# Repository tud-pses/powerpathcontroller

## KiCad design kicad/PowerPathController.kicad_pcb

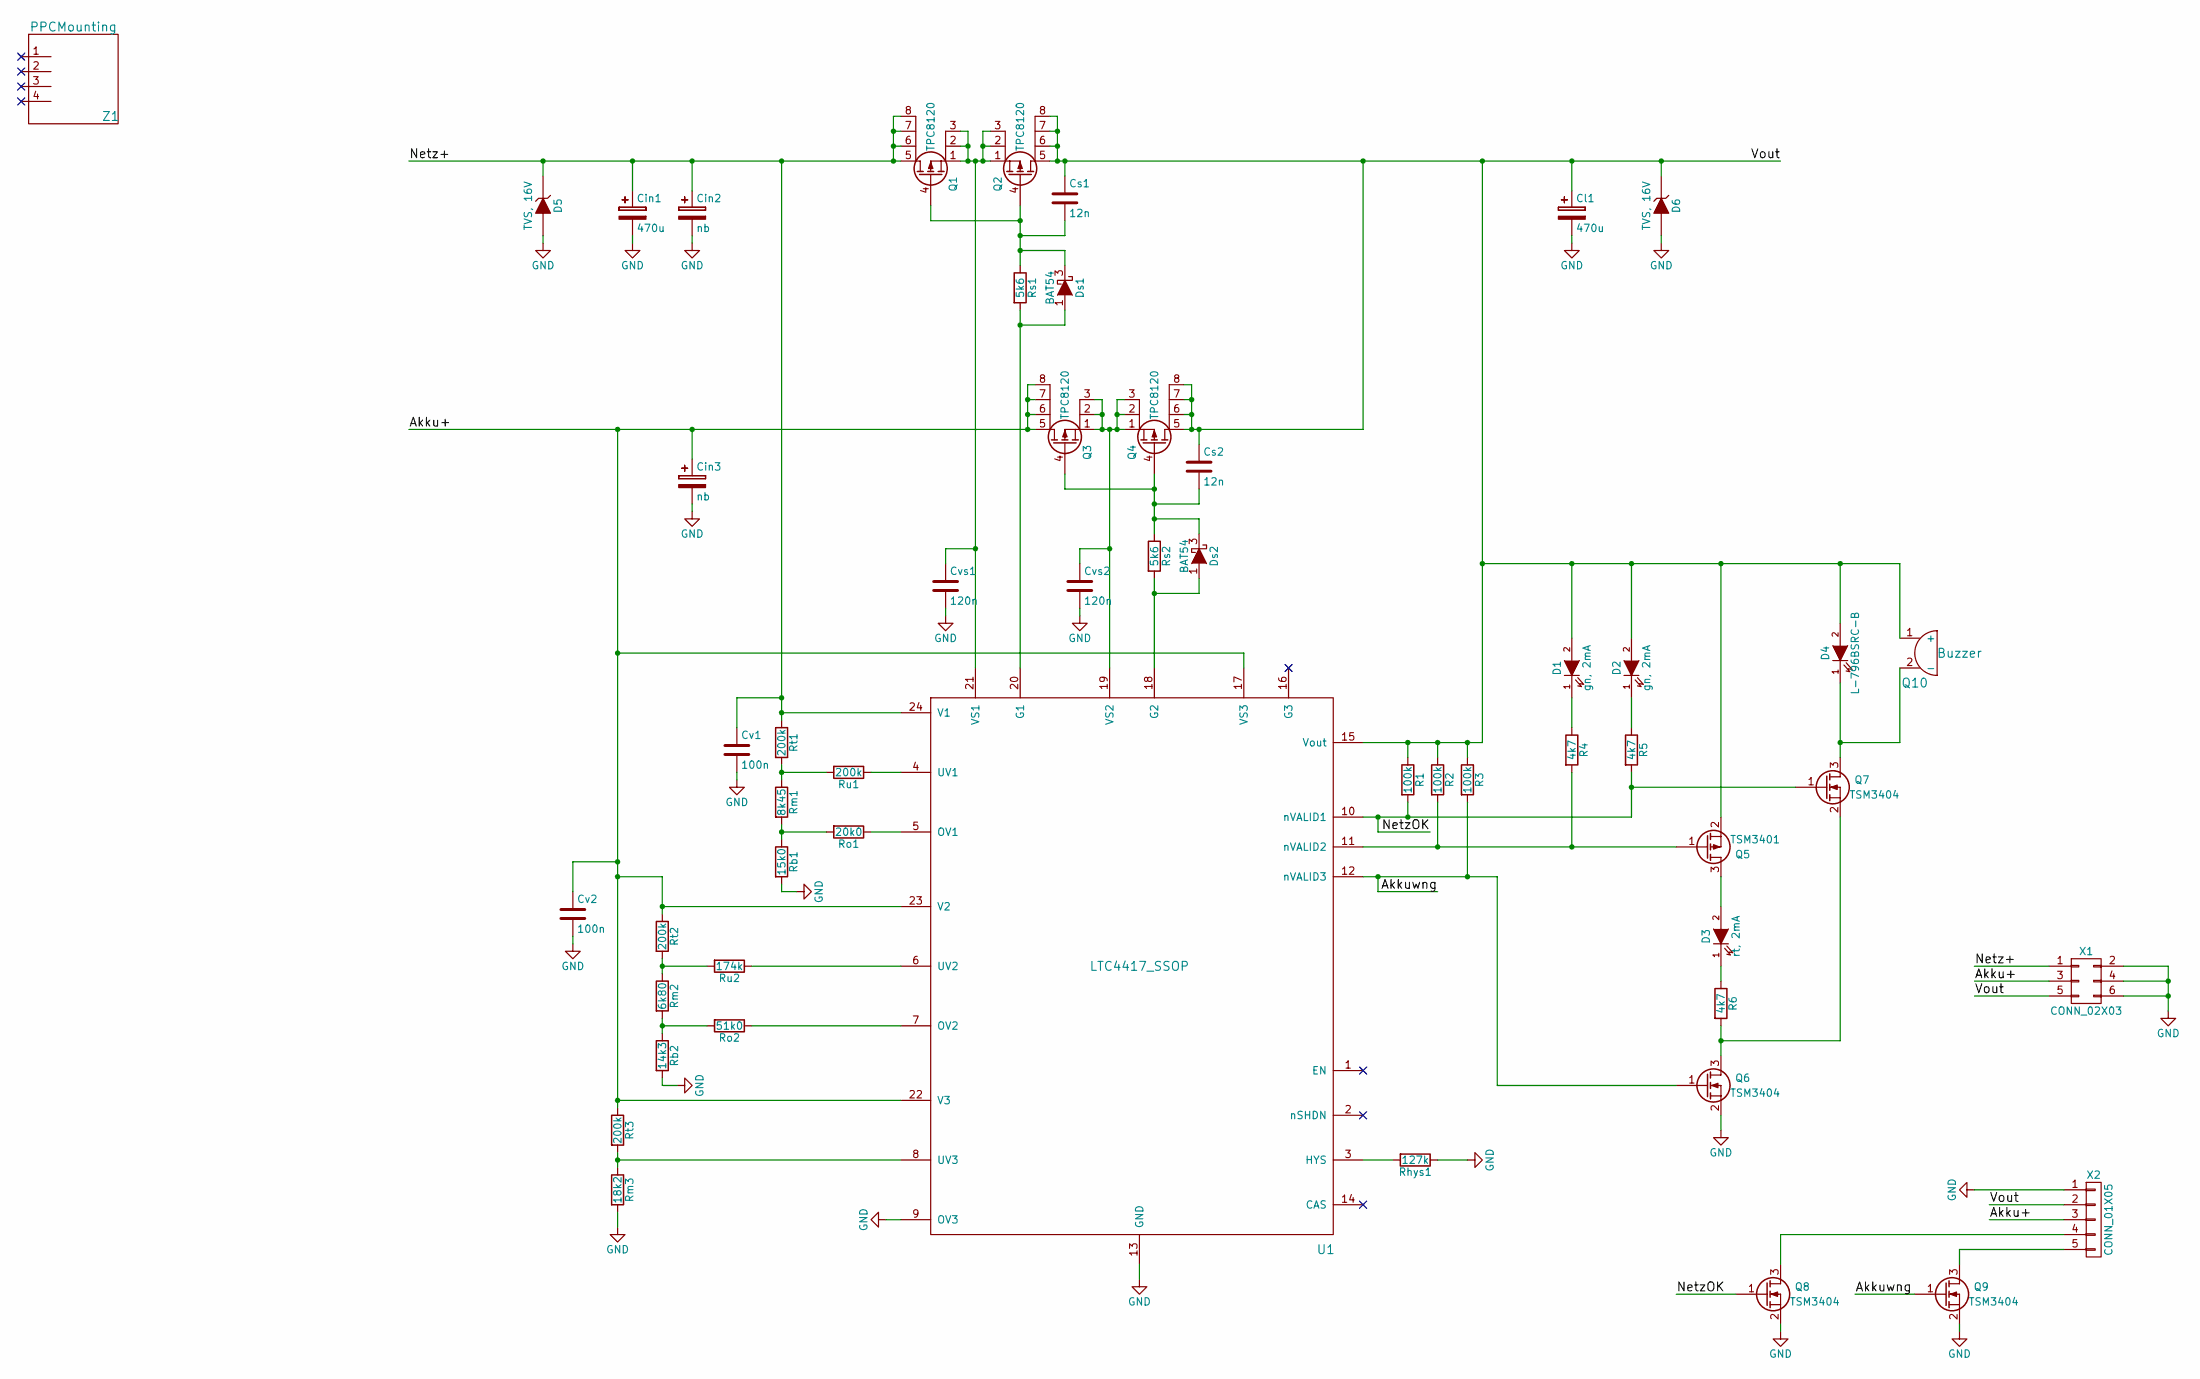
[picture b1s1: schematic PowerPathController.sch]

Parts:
Cin1: 470u; CPOL_12.5o8mm_5o3.5mm
Cin2: nb; CPOL_12.5o8mm_5o3.5mm
Cin3: nb; CPOL_8mm_3.5mm
Cl1: 470u; CPOL_12.5o8mm_5o3.5mm
Cs1, Cs2: 12n; C_0603_HandSoldering
Cv1, Cv2: 100n; C_0603_HandSoldering
Cvs1, Cvs2: 120n; C_0603_HandSoldering
D1, D2: gn, 2mA; LED-0603
D3: rt, 2mA; LED-0603
D4: L-796BSRC-B; LED-8MM_o_CONN_PS25_2G
D5, D6: TVS, 16V; SOD-123W
Ds1, Ds2: BAT54; SOT-23_Handsoldering
Q1, Q2, Q3, Q4: TPC8120; SOIC-8_3.9x4.9mm_Pitch1.27mm
Q5: TSM3401; SOT-23_Handsoldering
Q6, Q7, Q8, Q9: TSM3404; SOT-23_Handsoldering
Q10: Buzzer; Buzzer_AL-60P12
R1, R2, R3: 100k; R_0603_HandSoldering
R4, R5, R6: 4k7; R_0603_HandSoldering
Rb1: 15k0; R_0603_HandSoldering
Rb2: 14k3; R_0603_HandSoldering
Rhys1: 127k; R_0603_HandSoldering
Rm1: 8k45; R_0603_HandSoldering
Rm2: 6k80; R_0603_HandSoldering
Rm3: 18k2; R_0603_HandSoldering
Ro1: 20k0; R_0603_HandSoldering
Ro2: 51k0; R_0603_HandSoldering
Rs1, Rs2: 5k6; R_0603_HandSoldering
Rt1, Rt2, Rt3: 200k; R_0603_HandSoldering
Ru1: 200k; R_0603_HandSoldering
Ru2: 174k; R_0603_HandSoldering
U1: LTC4417_SSOP; SSOP-24_3.9x8.7mm_Pitch0.635mm
X1: CONN_02X03; WAGO_713-1403
X2: CONN_01X05; CONN_PS25_5G
Z1: PPCMounting; PPCMOUNTING

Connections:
/Akku+: Cin3.1, Cv2.1, Q3.5 (D), Q3.6 (D), Q3.7 (D), Q3.8 (D), Rt2.1, Rt3.1, U1.17 (VS3), U1.22 (V3), U1.23 (V2), X1.3, X2.3
/Akkuwng: Q6.1 (G), Q9.1 (G), R3.2, U1.12 (nVALID3)
/Netz+: Cin1.1, Cin2.1, Cv1.1, D5.1 (K), Q1.5 (D), Q1.6 (D), Q1.7 (D), Q1.8 (D), Rt1.1, U1.24 (V1), X1.1
/NetzOK: Q7.1 (G), Q8.1 (G), R1.2, R5.2, U1.10 (nVALID1)
/Vout: Cl1.1, Cs1.1, Cs2.1, D1.2 (A), D2.2 (A), D4.2 (A), D6.1 (K), Q2.5 (D), Q2.6 (D), Q2.7 (D), Q2.8 (D), Q4.5 (D), Q4.6 (D), Q4.7 (D), Q4.8 (D), Q5.2 (S), Q10.1 (+), R1.1, R2.1, R3.1, U1.15 (Vout), X1.5, X2.2
GND: Cin1.2, Cin2.2, Cin3.2, Cl1.2, Cv1.2, Cv2.2, Cvs1.2, Cvs2.2, D5.2 (A), D6.2 (A), Q6.2 (S), Q8.2 (S), Q9.2 (S), Rb1.2, Rb2.2, Rhys1.1, Rm3.2, U1.9 (OV3), U1.13 (GND), X1.2, X1.4, X1.6, X2.1
unnamed: Cs1.2, Ds1.3 (K), Q1.4 (G), Q2.4 (G), Rs1.1
unnamed: Cs2.2, Ds2.3 (K), Q3.4 (G), Q4.4 (G), Rs2.1
unnamed: Cvs1.1, Q1.1 (S), Q1.2 (S), Q1.3 (S), Q2.1 (S), Q2.2 (S), Q2.3 (S), U1.21 (VS1)
unnamed: Cvs2.1, Q3.1 (S), Q3.2 (S), Q3.3 (S), Q4.1 (S), Q4.2 (S), Q4.3 (S), U1.19 (VS2)
unnamed: D1.1 (K), R4.1
unnamed: D2.1 (K), R5.1
unnamed: D3.1 (K), R6.1
unnamed: D3.2 (A), Q5.3 (D)
unnamed: D4.1 (K), Q7.3 (D), Q10.2 (-)
unnamed: Ds1.1 (A), Rs1.2, U1.20 (G1)
unnamed: Ds2.1 (A), Rs2.2, U1.18 (G2)
unnamed: Q5.1 (G), R2.2, R4.2, U1.11 (nVALID2)
unnamed: Q6.3 (D), Q7.2 (S), R6.2
unnamed: Q8.3 (D), X2.4
unnamed: Q9.3 (D), X2.5
unnamed: Rb1.1, Rm1.2, Ro1.2
unnamed: Rb2.1, Rm2.2, Ro2.2
unnamed: Rhys1.2, U1.3 (HYS)
unnamed: Rm1.1, Rt1.2, Ru1.2
unnamed: Rm2.1, Rt2.2, Ru2.2
unnamed: Rm3.1, Rt3.2, U1.8 (UV3)
unnamed: Ro1.1, U1.5 (OV1)
unnamed: Ro2.1, U1.7 (OV2)
unnamed: Ru1.1, U1.4 (UV1)
unnamed: Ru2.1, U1.6 (UV2)

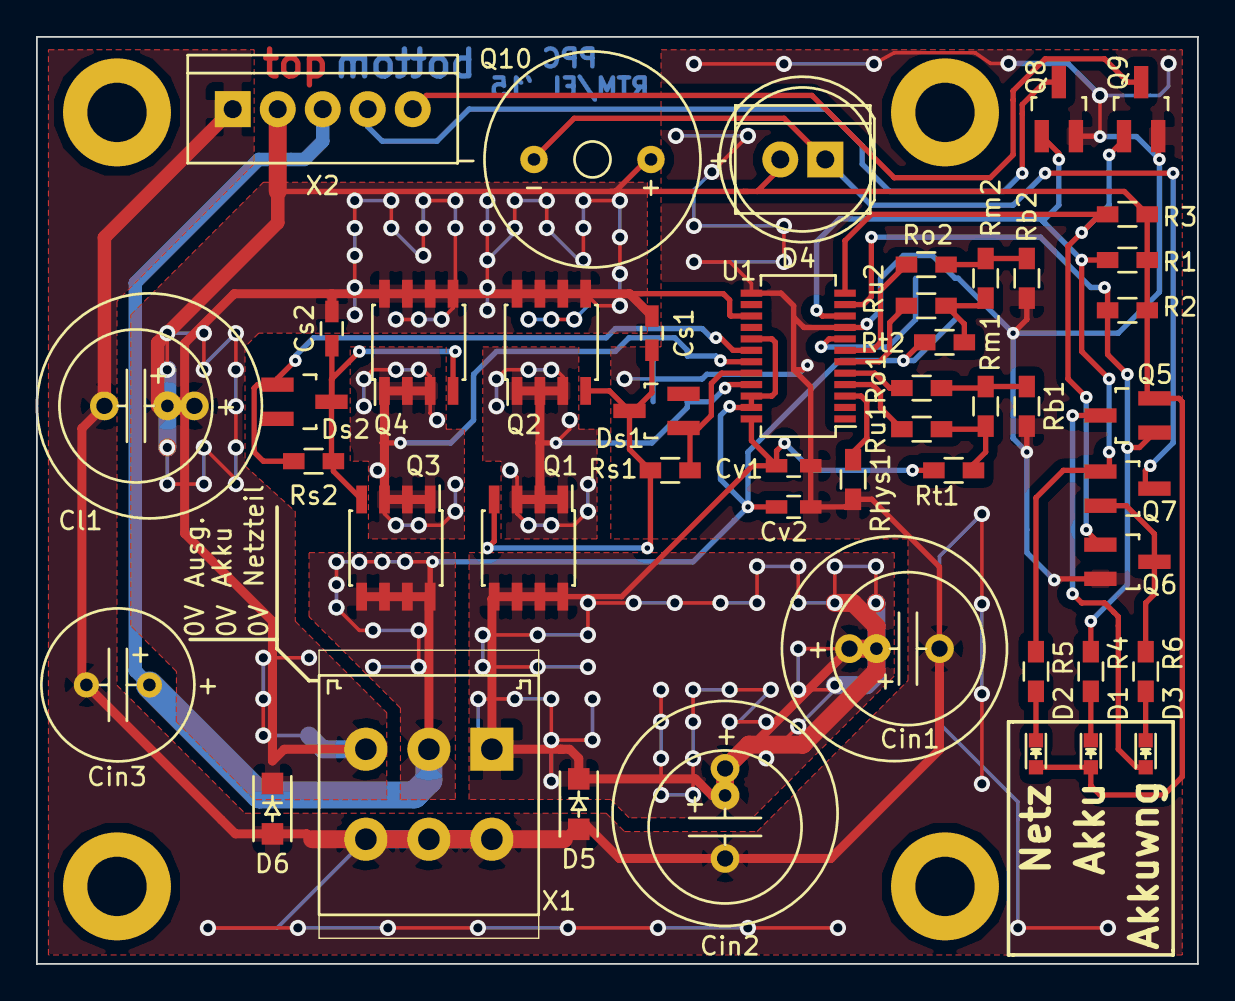
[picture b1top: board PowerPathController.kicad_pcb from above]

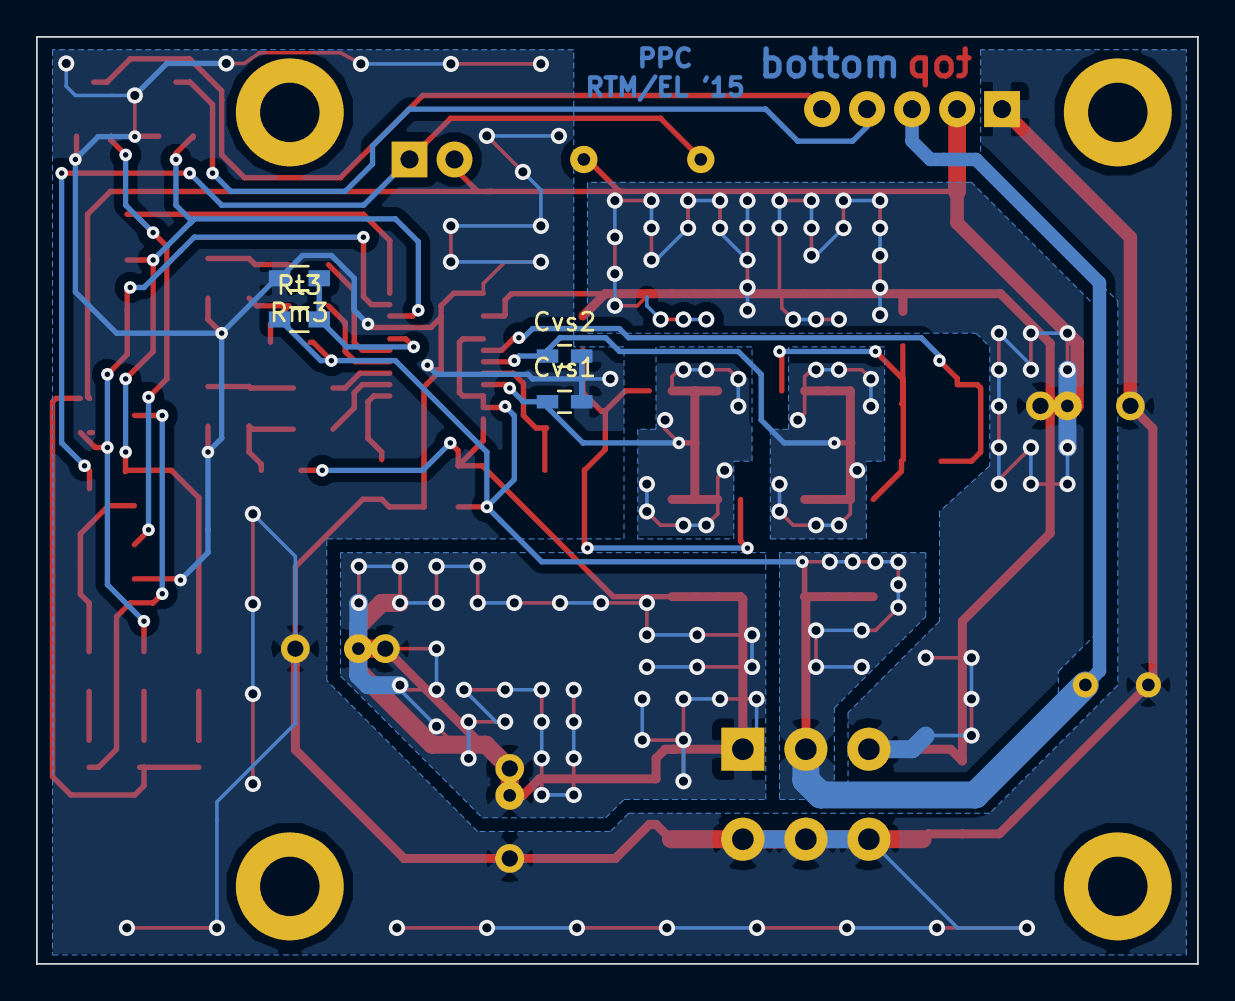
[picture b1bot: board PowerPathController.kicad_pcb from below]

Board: 2 copper layers, 64.5 x 51.5 mm, 53 parts (4 on the bottom side), 31 nets.

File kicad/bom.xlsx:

|  |  |  |  |  |  |  |  |  |  | Bestellung
 |  |  |  |  |  |  |  |  | 29.316900000000008 |  | Anzahl Platinen: | 2
 | Referenz | Bezeichnung/wesentliche Eigenschaften | Bauform | Bemerkung | Hersteller | Hersteller-Nr. | Lieferant | Lieferant-Nr. | Preis |  |  |  | Farnell | Reichelt
 | U1 | LTC4417 | SSOP 24 narrow |  | Linear | LTC4417IGN#PBF | Farnell | 2293163 | 9.17 |  |  |  | 2293163, 2
 | Cin1 | 470u, 25V | Footprint für RAD FR 1.500/35 geeignet | 35V |  |  | Reichelt | RAD FR 470/35 | 0.23 |  |  |  |  | RAD FR 470/35, 2
 | Cin2 | nb (470u, 25V vorsehen) | Footprint für RAD FR 1.500/35 geeignet | 35V
 | Cin3 | nb (220u, 25V vorsehen) |  | 35V
 | Cl1 | 470u, 25V | Footprint für RAD FR 1.500/35 geeignet | 35V |  |  | Reichelt | RAD FR 470/35 | 0.23 |  |  |  |  | RAD FR 470/35, 2
 | Cv1 | 100n, 25V | 0603 | X7R |  |  | Farnell | 1759037 | 7.0000000000000001E-3 |  |  |  | 1759037, 2
 | Cv2 | 100n, 25V | 0603 | X7R |  |  | Farnell | 1759037 | 7.0000000000000001E-3 |  |  |  | 1759037, 2
 | Cvs1 | 120n, 25V | 0603 | X7R, 50V |  |  | Farnell | 1793828 | 0.11 |  |  |  | 1793828, 2
 | Cvs2 | 120n, 25V | 0603 | X7R, 50V |  |  | Farnell | 1793828 | 0.11 |  |  |  | 1793828, 2
 | Cs1 | 12n, 25V | 0603 | X7R, 50V |  |  | Farnell | 1865534 | 4.3099999999999999E-2 |  |  |  | 1865534, 2
 | Cs2 | 12n, 25V | 0603 | X7R, 50V |  |  | Farnell | 1865534 | 4.3099999999999999E-2 |  |  |  | 1865534, 2
 | Rt1 | 200k | 0603 | 1% |  |  | Farnell | 1469776 | 1.26E-2 |  |  |  | 1469776, 2
 | Rm1 | 8k45 | 0603 | 1% |  |  | Farnell | 2138418 | 1.26E-2 |  |  |  | 2138418, 2
 | Rb1 | 15k0 | 0603 | 1% |  |  | Farnell | 1469758 | 1.1599999999999999E-2 |  |  |  | 1469758, 2
 | Ru1 | 200k | 0603 | 1% |  |  | Farnell | 1469776 | 1.26E-2 |  |  |  | 1469776, 2
 | Ro1 | 20k0 | 0603 | 1% |  |  | Farnell | 1469774 | 1.7000000000000001E-2 |  |  |  | 1469774, 2
 | Rt2 | 200k | 0603 | 1% |  |  | Farnell | 1469776 | 1.26E-2 |  |  |  | 1469776, 2
 | Rm2 | 6k80 | 0603 | 1% |  |  | Farnell | 1469831 | 1.26E-2 |  |  |  | 1469831, 2
 | Rb2 | 14k3 | 0603 | 1% |  |  | Farnell | 2138430 | 1.0500000000000001E-2 |  |  |  | 2138430, 2
 | Ru2 | 174k | 0603 | 1% |  |  | Farnell | 2138522 | 1.7999999999999999E-2 |  |  |  | 2138522, 2
 | Ro2 | 51k0 | 0603 | 1% |  |  | Farnell | 1469822 | 1.1599999999999999E-2 |  |  |  | 1469822, 2
 | Rt3 | 200k | 0603 | 1% |  |  | Farnell | 1469776 | 1.26E-2 |  |  |  | 1469776, 2
 | Rm3 | 18k2 | 0603 | 1% |  |  | Farnell | 1652845 | 1.26E-2 |  |  |  | 1652845, 2
 | _Rm3 | 18k2 | 0603 | 1% |  |  | Farnell | 1527611 | 8.0799999999999997E-2 |  |  |  | 1527611, 2
 | Rhys1 | 127k | 0603 | 1% |  |  | Farnell | 2138509 | 1.7999999999999999E-2 |  |  |  | 2138509, 2
 | R1 | 100k | 0603 | 1% |  |  | Reichelt | SMD-0603 100K | 0.08 |  |  |  |  | SMD-0603 100K, 2
 | R2 | 100k | 0603 | 1% |  |  | Reichelt | SMD-0603 100K | 0.08 |  |  |  |  | SMD-0603 100K, 2
 | R3 | 100k | 0603 | 1% |  |  | Reichelt | SMD-0603 100K | 0.08 |  |  |  |  | SMD-0603 100K, 2
 | R4 | 4k7 | 0603 | 1% |  |  | Reichelt | SMD-0603 4,7K | 0.08 |  |  |  |  | SMD-0603 4,7K, 2
 | R5 | 4k7 | 0603 | 1% |  |  | Reichelt | SMD-0603 4,7K | 0.08 |  |  |  |  | SMD-0603 4,7K, 2
 | R6 | 4k7 | 0603 | 1% |  |  | Reichelt | SMD-0603 4,7K | 0.08 |  |  |  |  | SMD-0603 4,7K, 2
 | Rs1 | 5k6 | 0603 | 1% |  |  | Reichelt | SMD-0603 5,6K | 0.08 |  |  |  |  | SMD-0603 5,6K, 2
 | Rs2 | 5k6 | 0603 | 1% |  |  | Reichelt | SMD-0603 5,6K | 0.08 |  |  |  |  | SMD-0603 5,6K, 2
 | D1 | LED, gn, 2mA | 0603 |  | Osram | LG L29K | Reichelt | LG L29K | 0.18 |  |  |  |  | LG L29K, 2
 | D2 | LED, gn, 2mA | 0603 |  | Osram | LG L29K | Reichelt | LG L29K | 0.18 |  |  |  |  | LG L29K, 2
 | D3 | LED, rt, 2mA | 0603 |  | Osram | LS L29K | Reichelt | LS L29K | 0.14000000000000001 |  |  |  |  | LS L29K, 2
 | D4 | Blink-LED, max 12,25 V, min 10 V |  | 8 mm, 800 mcd, 40° Abstrahlwinkel | Kingbright | L-796BSRC-B | Farnell | 1168559 | 0.746 |  |  |  | 1168559, 2
 | _D4 | Blink-LED, max 12,25 V, min 10 V |  | 5 mm, 200 mcd, 60° Abstrahlwinkel | Lumex | SSL-LX5093BSRD | Farnell | 2062466 | 0.78500000000000003 |  |  |  | 2062466, 2
 | _D4 | Stecker, 2-polig |  |  |  |  | Reichelt | PS 25/2G BR | 0.27 |  |  |  |  | PS 25/2G BR, 2
 | Ds1 | BAT54 | SOT-23 |  |  |  | Reichelt | BAT 54 SMD | 0.04 |  |  |  |  | BAT 54 SMD, 2
 | Ds2 | BAT54 | SOT-23 |  |  |  | Reichelt | BAT 54 SMD | 0.04 |  |  |  |  | BAT 54 SMD, 2
 | D5 | TVS, unidirektional, 16V | SOD123W | ClampVoltage: 26V | NXP | PTVS16VS1UR | Farnell | 1829241 | 0.14000000000000001 |  |  |  | 1829241, 2
 | D6 | TVS, unidirektional, 16V | SOD123W | ClampVoltage: 26V | NXP | PTVS16VS1UR | Farnell | 1829241 | 0.14000000000000001 |  |  |  | 1829241, 2
 | Q1 | TPC8120 | SOP 8 |  | Toshiba | TPC8120 | Farnell | 1901967 | 2.17 |  |  |  | 1901967, 2
 | Q2 | TPC8120 | SOP 8 |  | Toshiba | TPC8120 | Farnell | 1901967 | 2.17 |  |  |  | 1901967, 2
 | Q3 | TPC8120 | SOP 8 |  | Toshiba | TPC8120 | Farnell | 1901967 | 2.17 |  |  |  | 1901967, 2
 | Q4 | TPC8120 | SOP 8 |  | Toshiba | TPC8120 | Farnell | 1901967 | 2.17 |  |  |  | 1901967, 2
 | Q5 | TSM3401 | SOT 23 |  |  |  | Reichelt | TSM 3401 SMD | 0.25 |  |  |  |  | TSM 3401 SMD, 2
 | Q6 | TSM3404 | SOT 23 |  |  |  | Reichelt | TSM 3404 SMD | 0.25 |  |  |  |  | TSM 3404 SMD, 2
 | Q7 | TSM3404 | SOT 23 |  |  |  | Reichelt | TSM 3404 SMD | 0.25 |  |  |  |  | TSM 3404 SMD, 2
 | Q8 | TSM3404 | SOT 23 |  |  |  | Reichelt | TSM 3404 SMD | 0.25 |  |  |  |  | TSM 3404 SMD, 2
 | Q9 | TSM3404 | SOT 23 |  |  |  | Reichelt | TSM 3404 SMD | 0.25 |  |  |  |  | TSM 3404 SMD, 2
 | Q10 | Summer, max 12,25 V, min 10 V |  |  | Ekulit | AL-60SP12 | Conrad | 710146 | 0.85
 | X1 | Leistungsstecker, 2 x 3-polig |  | 10 A |  |  | Reichelt | WAGO 713-1403 | 1.2 |  |  |  |  | WAGO 713-1403, 2
 | X2 | Stecker uC, 5 polig |  | 3 A |  |  | Reichelt | PS 25/5G BR | 0.63 |  |  |  |  | PS 25/5G BR, 2
 |  | Buchse für X1 |  |  |  |  | Reichelt | WAGO 713-1103 | 3.2 |  |  |  |  | WAGO 713-1103, 2

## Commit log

2018-07-06 start ppc-repository
